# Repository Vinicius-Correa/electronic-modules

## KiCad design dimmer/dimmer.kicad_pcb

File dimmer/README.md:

## KiCad Project - Dimmer Module

Schematic:

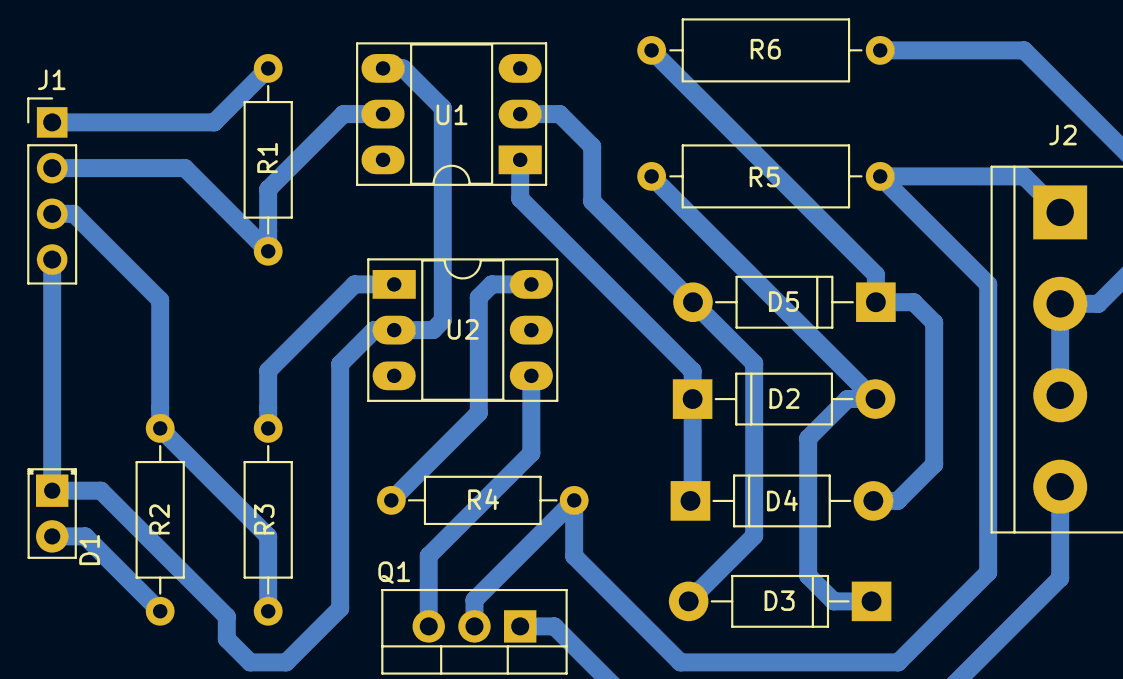
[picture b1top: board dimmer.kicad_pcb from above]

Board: 2 copper layers, 16 parts (0 on the bottom side), 15 nets.

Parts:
D1: LED; LED_D2.0mm_W4.8mm_H2.5mm_FlatTop
D2, D3, D4, D5: 1N4007; D_DO-41_SOD81_P10.16mm_Horizontal
J1: Conn_01x04; Pin_Header_Straight_1x04_Pitch2.54mm
J2: Conn_01x04; TerminalBlock_bornier-4_P5.08mm
Q1: TIC216; TO-220-3_Vertical
R1, R4: 1k; R_Axial_DIN0207_L6.3mm_D2.5mm_P10.16mm_Horizontal
R2: 470; R_Axial_DIN0207_L6.3mm_D2.5mm_P10.16mm_Horizontal
R3: 330; R_Axial_DIN0207_L6.3mm_D2.5mm_P10.16mm_Horizontal
R5, R6: 15k/1W; R_Axial_DIN0309_L9.0mm_D3.2mm_P12.70mm_Horizontal
U1: 4N25; DIP-6_W7.62mm_Socket_LongPads
U2: MOC3021M; DIP-6_W7.62mm_Socket_LongPads

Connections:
GND: D1.1, J1.4, U1.4, U2.2
NEUT: J2.2, J2.3, R6.1
unnamed: D1.2, R2.2
unnamed: D2.1, D4.1, U1.1
unnamed: D2.2, D3.1, R5.2
unnamed: D3.2, D5.2, U1.2
unnamed: D4.2, D5.1, R6.2
unnamed: J2.4, Q1.1
unnamed: Q1.3, U2.4
unnamed: R3.1, U2.1
unnamed: R4.2, U2.6
VAC: J2.1, Q1.2, R4.1, R5.1
VCC: J1.1, R1.1
dimmer: J1.3, R2.1, R3.2
zero-c: J1.2, R1.2, U1.5

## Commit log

2019-03-06 pcb finished
2019-03-07 update resistences 1W values
2019-03-07 update headers
2019-03-08 upated dimmer track
